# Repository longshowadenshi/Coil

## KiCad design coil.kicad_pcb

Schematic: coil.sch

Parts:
C1: 100uF/16V; C_D5
CN1: B3B-XH-A; XH-3pins
CN2, CN3: B2B-XH-A; XH-2pins
LED1, LED2: Led_SLI; led-os
MJ-179P1: MJ-179P; MJ179P
Q1, Q2: 2SC1815; TO-92_Inline
R1: 1k; R
R2: 10k; R
R3: 7.2k; R
R4: 7.4k; R
R5: 200; R
SW1: SKHHBY
U1: coil; socket-3pins

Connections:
+9V: C1.1, CN1.1, CN2.1, CN3.1, R2.1, R3.1, R4.1, R5.1, SW1.3, SW1.4
GND: C1.2, CN1.2, CN2.2, CN3.2, LED2.2, MJ-179P1.2, MJ-179P1.3, Q1.1, Q2.1, U1.3
unnamed: CN1.3, R1.2
unnamed: LED1.1, R3.2
unnamed: LED1.2, Q2.2
unnamed: LED2.1, R4.2
unnamed: MJ-179P1.1, SW1.1, SW1.2
unnamed: Q1.2, Q2.3, R2.2
unnamed: Q1.3, R1.1
unnamed: R5.2, U1.1

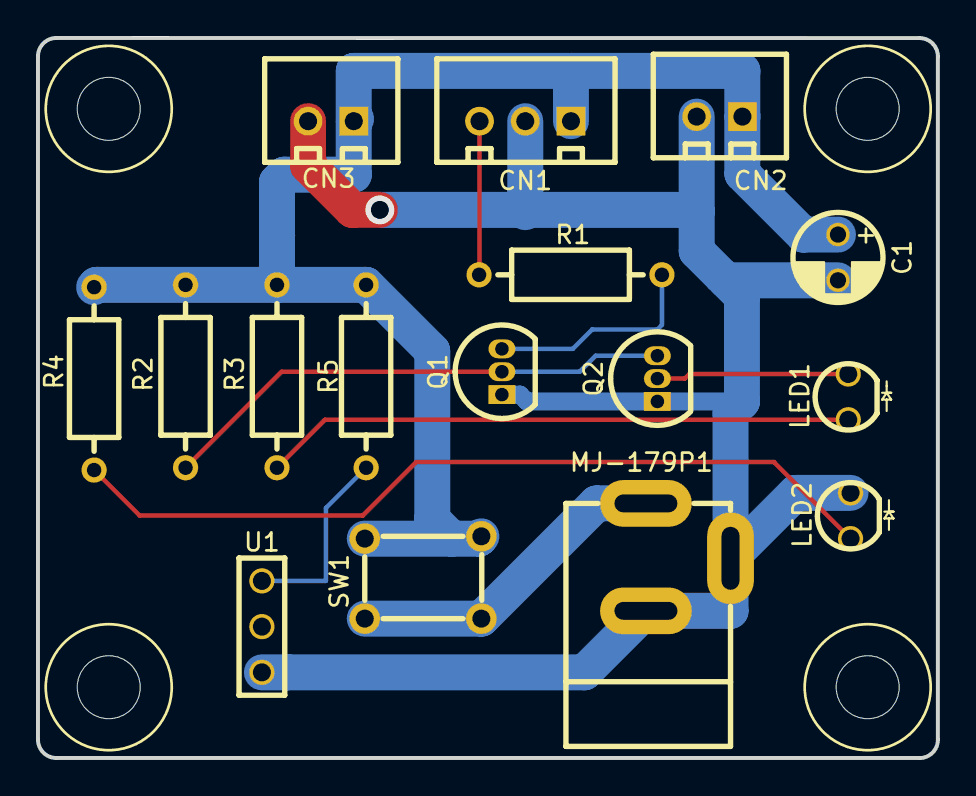
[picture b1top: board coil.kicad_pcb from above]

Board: 2 copper layers, 50.0 x 40.0 mm, 16 parts (0 on the bottom side), 10 nets.
